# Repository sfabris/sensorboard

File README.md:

Sensor Board to be used with OpenXsensor (https://code.google.com/p/openxsensor/)

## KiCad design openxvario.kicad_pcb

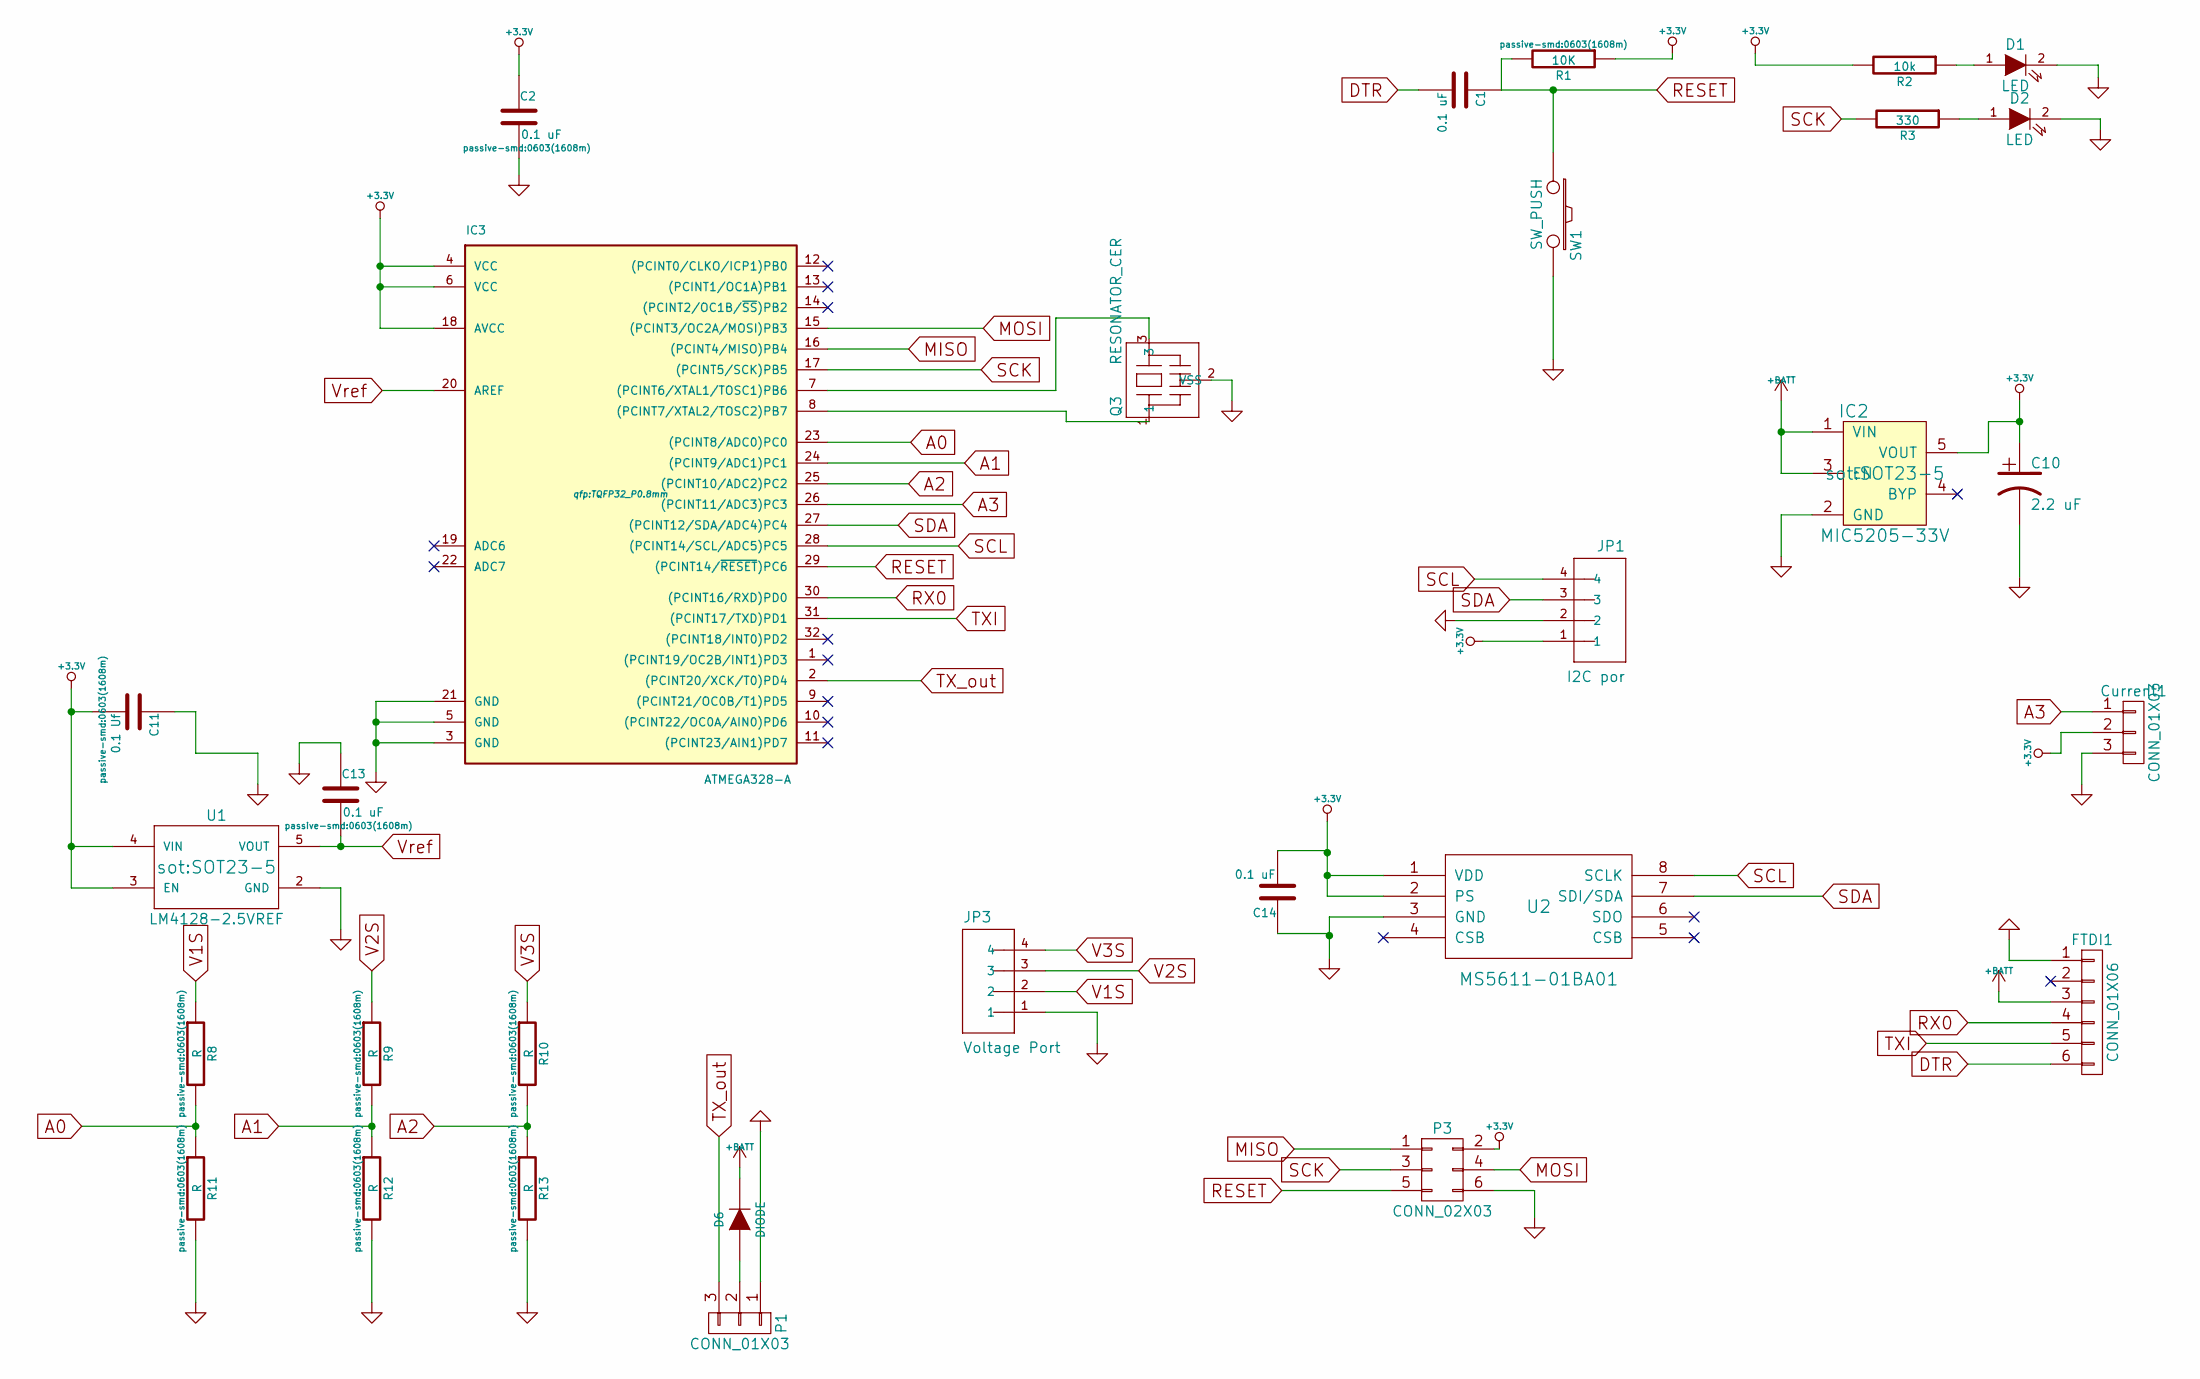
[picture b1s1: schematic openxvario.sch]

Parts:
C1, C2, C13, C14: 0.1 uF; 0603(1608m)
C10: 2.2 uF; SMD-0603_c
C11: 0.1 Uf; 0603(1608m)
Current1: CONN_01X03; Pin_Header_Straight_1x03
D1, D2: LED; 0603(1608m)-SM-LED
D6: DIODE; SOT23
FTDI1: CONN_01X06; Pin_Header_Straight_1x06
IC2: MIC5205-33V; SOT23-5
IC3: ATMEGA328-A; TQFP32_P0.8mm
JP1: I2C por; con-jst2-BM04B-SRSS-TB
JP3: Voltage Port; Pin_Header_Straight_1x04
P1: CONN_01X03; Pin_Header_Straight_1x03
P3: CONN_02X03; Pin_Header_Straight_2x03
Q3: RESONATOR_CER; SparkFun-RESONATOR-SMD
R1: 10K; 0603(1608m)
R2: 10k; 0603(1608m)
R3: 330; 0603(1608m)
R8, R9, R10, R11, R12, R13: R; 0603(1608m)
SW1: SW_PUSH; SparkFun-TACTILE-SWITCH-1101NE
U1: LM4128-2.5VREF; SOT23-5
U2: MS5611-01BA01

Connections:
+3.3V: C2.1, C10.1, C11.2, C14.2, Current1.2, IC2.5 (VOUT), IC3.4 (VCC), IC3.6 (VCC), IC3.18 (AVCC), JP1.1, P3.2, R1.1, R2.2, U1.3 (EN), U1.4 (VIN), U2.1 (VDD), U2.2 (PS); also elsewhere on the board
+BATT: D6.2 (K), FTDI1.3, IC2.1 (VIN), IC2.3 (EN)
A0: IC3.23 ((PCINT8/ADC0)PC0), R8.2, R11.1
A1: IC3.24 ((PCINT9/ADC1)PC1), R9.2, R12.1
A2: IC3.25 ((PCINT10/ADC2)PC2), R10.2, R13.1
A3: Current1.1, IC3.26 ((PCINT11/ADC3)PC3)
DTR: C1.2, FTDI1.6
GND: C2.2, C10.2, C11.1, C13.1, C14.1, Current1.3, D1.2 (K), D2.2 (K), FTDI1.1, IC2.2 (GND), IC3.3 (GND), IC3.5 (GND), IC3.21 (GND), JP1.2, JP3.1, P1.1, P3.6, Q3.2 (VSS), R11.2, R12.2, R13.2, SW1.2, U1.2 (GND), U2.3 (GND); also elsewhere on the board
MISO: IC3.16 ((PCINT4/MISO)PB4), P3.1; also elsewhere on the board
MOSI: IC3.15 ((PCINT3/OC2A/MOSI)PB3), P3.4; also elsewhere on the board
unnamed: D1.1 (A), R2.1
unnamed: D2.1 (A), R3.1
unnamed 12: D6.1 (A), P1.2; also elsewhere on the board
unnamed: IC3.7 ((PCINT6/XTAL1/TOSC1)PB6), Q3.3
unnamed: IC3.8 ((PCINT7/XTAL2/TOSC2)PB7), Q3.1
RESET: C1.1, IC3.29 ((PCINT14/~RESET~)PC6), P3.5, R1.2, SW1.1; also elsewhere on the board
RX0: FTDI1.4, IC3.30 ((PCINT16/RXD)PD0)
SCK: IC3.17 ((PCINT5/SCK)PB5), P3.3, R3.2; also elsewhere on the board
SCL: IC3.28 ((PCINT14/SCL/ADC5)PC5), JP1.4, U2.8 (SCLK)
SDA: IC3.27 ((PCINT12/SDA/ADC4)PC4), JP1.3, U2.7 (SDI/SDA)
TXI: FTDI1.5, IC3.31 ((PCINT17/TXD)PD1)
TX_out: IC3.2 ((PCINT20/XCK/T0)PD4), P1.3; also elsewhere on the board
V1S: JP3.2, R8.1; also elsewhere on the board
V2S: JP3.3, R9.1; also elsewhere on the board
V3S: JP3.4, R10.1; also elsewhere on the board
Vref: C13.2, IC3.20 (AREF), U1.5 (VOUT)

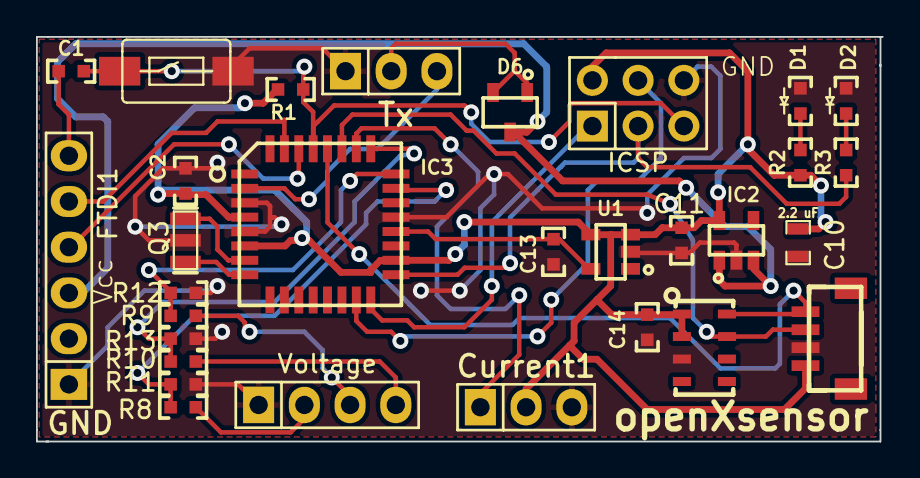
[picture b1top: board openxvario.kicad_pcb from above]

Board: 2 copper layers, 47.0 x 22.5 mm, 30 parts (0 on the bottom side), 26 nets.

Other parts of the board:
ICSP: CONN_02X03; Pin_Header_Straight_2x03
Tx: CONN_01X03; Pin_Header_Straight_1x03
Voltage: Voltage Port; Pin_Header_Straight_1x04

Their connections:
+3.3V: ICSP.2; also elsewhere on the board
GND: ICSP.6, Tx.1, Voltage.1; also elsewhere on the board
MISO: ICSP.1; also elsewhere on the board
MOSI: ICSP.4; also elsewhere on the board
unnamed 12: Tx.2; also elsewhere on the board
RESET: ICSP.5; also elsewhere on the board
SCK: ICSP.3; also elsewhere on the board
TX_out: Tx.3; also elsewhere on the board
V1S: Voltage.2; also elsewhere on the board
V2S: Voltage.3; also elsewhere on the board
V3S: Voltage.4; also elsewhere on the board

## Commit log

2015-02-13 Added README.md
2015-02-13 Adding libraries
2015-02-13 Adding cache-lib for missing libraries
2015-02-13 Adjusted libraries paths
2015-02-13 Added schematic and board pdfs
2015-02-13 Added actual picture of the assembled board
2015-02-24 Lost commit
